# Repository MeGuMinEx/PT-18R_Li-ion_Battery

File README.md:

# Brother PT-18R Li_ion Battery

## 在使用Brother PT-18R时受到镍氢电池的影响，导致经常出现打印到一半掉电，故设计此改装件

#### 硬件结构

* CH32V002F4U6主控制器
* 基于SGM6611的Boost输出(兼容TPS61089)
* 基于SGM41523B进行充电管理
* 集成锂电池保护芯片
* 复用原机电源接口，并且可复用该接口进行充电与放电功能
* 复用原机电池位，不影响盖板安装
* 支持原机座充
* 最大支持18650锂电池

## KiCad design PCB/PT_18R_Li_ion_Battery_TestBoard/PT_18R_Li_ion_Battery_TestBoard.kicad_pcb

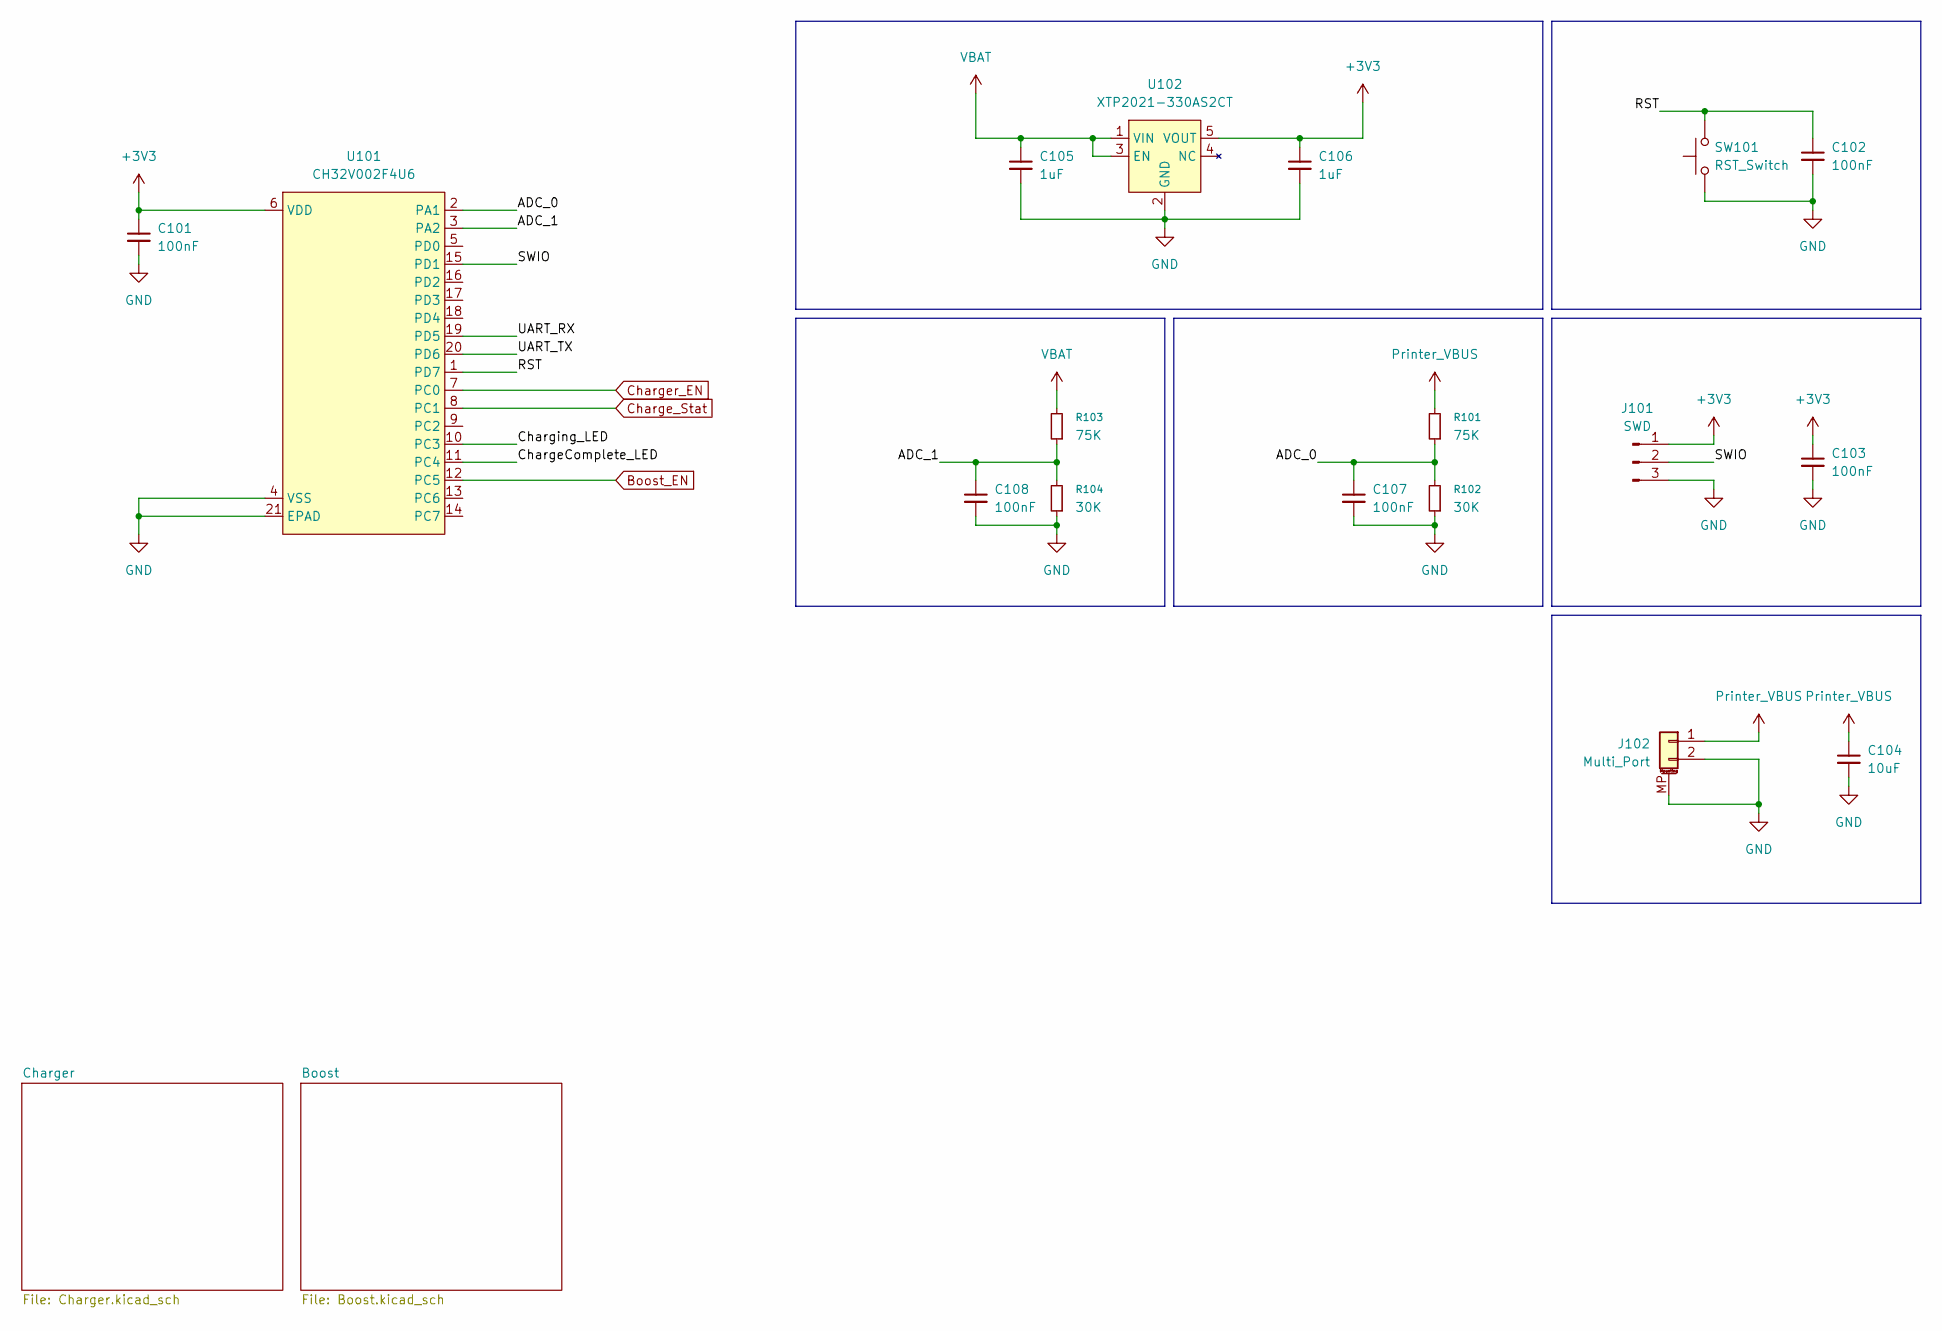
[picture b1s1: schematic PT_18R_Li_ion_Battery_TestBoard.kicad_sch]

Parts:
C101, C102, C103, C107, C108: 100nF; C_0603_1608Metric
C104: 10uF; C_0805_2012Metric
C105, C106: 1uF; C_0603_1608Metric
J101: SWD; PinHeader_1x03_P2.54mm_Vertical
J102: Multi_Port; TerminalBlock_Xinya_XY308-2.54-2P_1x02_P2.54mm_Horizontal
R101, R103: 75K; R_0603_1608Metric
R102, R104: 30K; R_0603_1608Metric
SW101: RST_Switch; SW_SPST_PTS645Sx43SMTR92
U101: CH32V002F4U6; QFN-20-1EP_3x3mm_P0.4mm_EP1.65x1.65mm_ThermalVias
U102: XTP2021-330AS2CT; SOT-23-5_HandSoldering

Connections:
+3V3: C101.1, C103.1, C106.1, J101.1, U101.6 (VDD), U102.5 (VOUT)
/ADC_0: C107.1, R101.1, R102.2, U101.2 (PA1)
/ADC_1: C108.1, R103.1, R104.2, U101.3 (PA2)
/ChargeComplete_LED: U101.11 (PC4)
/Charging_LED: U101.10 (PC3)
/RST: C102.1, SW101.2, U101.1 (PD7)
/SWIO: J101.2, U101.15 (PD1)
/UART_RX: U101.19 (PD5)
/UART_TX: U101.20 (PD6)
Boost_EN: U101.12 (PC5); also elsewhere on the board
Charge_Stat: U101.8 (PC1); also elsewhere on the board
Charger_EN: U101.7 (PC0); also elsewhere on the board
GND: C101.2, C102.2, C103.2, C104.2, C105.2, C106.2, C107.2, C108.2, J101.3, J102.2, J102.MP (MountPin), R102.1, R104.1, SW101.1, U101.4 (VSS), U101.21 (EPAD), U102.2 (GND); also elsewhere on the board
Printer_VBUS: C104.1, J102.1, R101.2; also elsewhere on the board
VBAT: C105.1, R103.2, U102.1 (VIN), U102.3 (EN); also elsewhere on the board

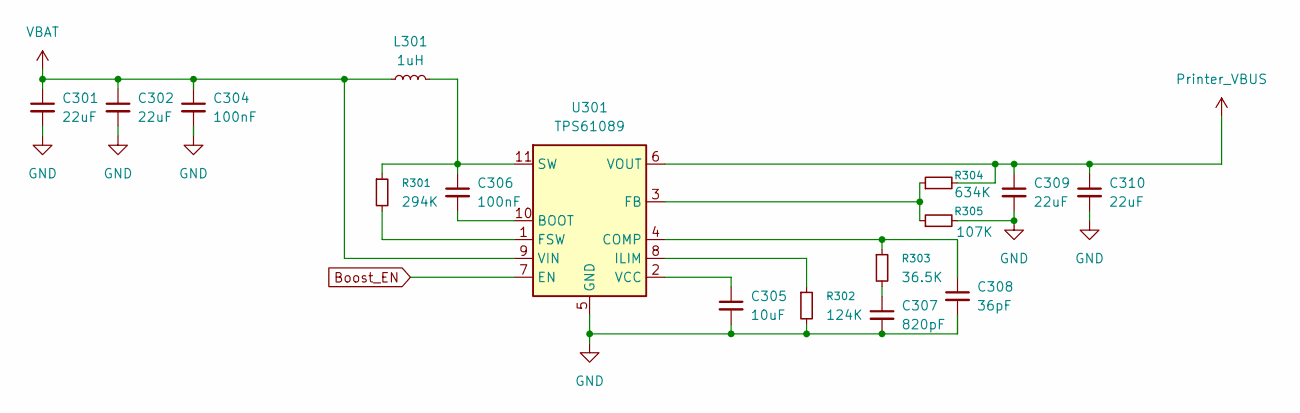
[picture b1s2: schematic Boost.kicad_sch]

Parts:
C301, C302, C309, C310: 22uF; C_0805_2012Metric
C304, C306: 100nF; C_0603_1608Metric
C305: 10uF; C_0805_2012Metric
C307: 820pF; C_0603_1608Metric
C308: 36pF; C_0603_1608Metric
L301: 1uH; L_1008_2520Metric
R301: 294K; R_0603_1608Metric
R302: 124K; R_0603_1608Metric
R303: 36.5K; R_0603_1608Metric
R304: 634K; R_0603_1608Metric
R305: 107K; R_0603_1608Metric
U301: TPS61089; Texas_VQFN-RNR0011A-11

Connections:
Boost_EN: U301.7 (EN); also elsewhere on the board
GND: C301.2, C302.2, C304.2, C305.2, C307.2, C308.2, C309.2, C310.2, R302.2, R305.2, U301.5 (GND); also elsewhere on the board
unnamed: C307.1, R303.2
unnamed: C306.2, U301.10 (BOOT)
unnamed: C308.1, R303.1, U301.4 (COMP)
unnamed: R304.1, R305.1, U301.3 (FB)
unnamed: R301.2, U301.1 (FSW)
unnamed: R302.1, U301.8 (ILIM)
unnamed: C306.1, L301.2, R301.1, U301.11 (SW)
unnamed: C305.1, U301.2 (VCC)
Printer_VBUS: C309.1, C310.1, R304.2, U301.6 (VOUT); also elsewhere on the board
VBAT: C301.1, C302.1, C304.1, L301.1, U301.9 (VIN); also elsewhere on the board

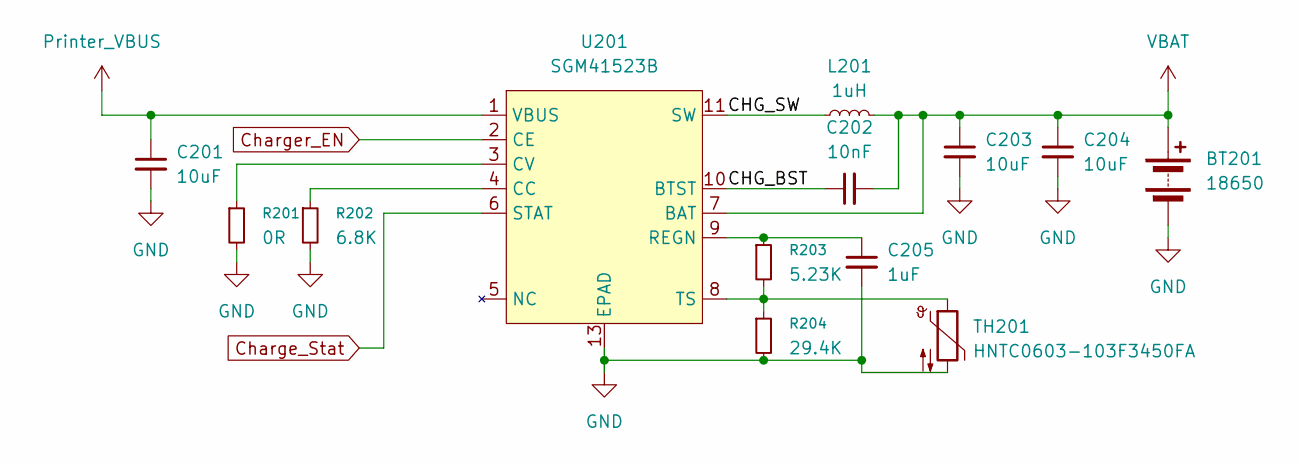
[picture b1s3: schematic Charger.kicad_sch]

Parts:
BT201: 18650; BatteryHolder_Keystone_1042_1x18650
C201, C203, C204: 10uF; C_0805_2012Metric
C202: 10nF; C_0603_1608Metric
C205: 1uF; C_0603_1608Metric
L201: 1uH; L_1008_2520Metric
R201: 0R; R_0603_1608Metric
R202: 6.8K; R_0603_1608Metric
R203: 5.23K; R_0603_1608Metric
R204: 29.4K; R_0603_1608Metric
TH201: HNTC0603-103F3450FA; R_0603_1608Metric
U201: SGM41523B; TDFN-12-1EP_3x3mm_P0.4mm_EP1.7x2.45mm_ThermalVias

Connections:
/Charger/CHG_BST: C202.1, U201.10 (BTST)
/Charger/CHG_SW: L201.1, U201.11 (SW), U201.12 (SW)
Charge_Stat: U201.6 (STAT); also elsewhere on the board
Charger_EN: U201.2 (CE); also elsewhere on the board
GND: BT201.2 (-), C201.2, C203.2, C204.2, C205.2, R201.2, R202.2, R204.2, TH201.2, U201.13 (EPAD); also elsewhere on the board
unnamed: R202.1, U201.4 (CC)
unnamed: R201.1, U201.3 (CV)
unnamed: C205.1, R203.1, U201.9 (REGN)
unnamed: R203.2, R204.1, TH201.1, U201.8 (TS)
Printer_VBUS: C201.1, U201.1 (VBUS); also elsewhere on the board
VBAT: BT201.1 (+), C202.2, C203.1, C204.1, L201.2, U201.7 (BAT); also elsewhere on the board

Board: 2 copper layers, 46 parts (0 on the bottom side), 25 nets, no tracks yet.

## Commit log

2026-03-20 Project Init
2026-03-22 原理图完成，待布局
